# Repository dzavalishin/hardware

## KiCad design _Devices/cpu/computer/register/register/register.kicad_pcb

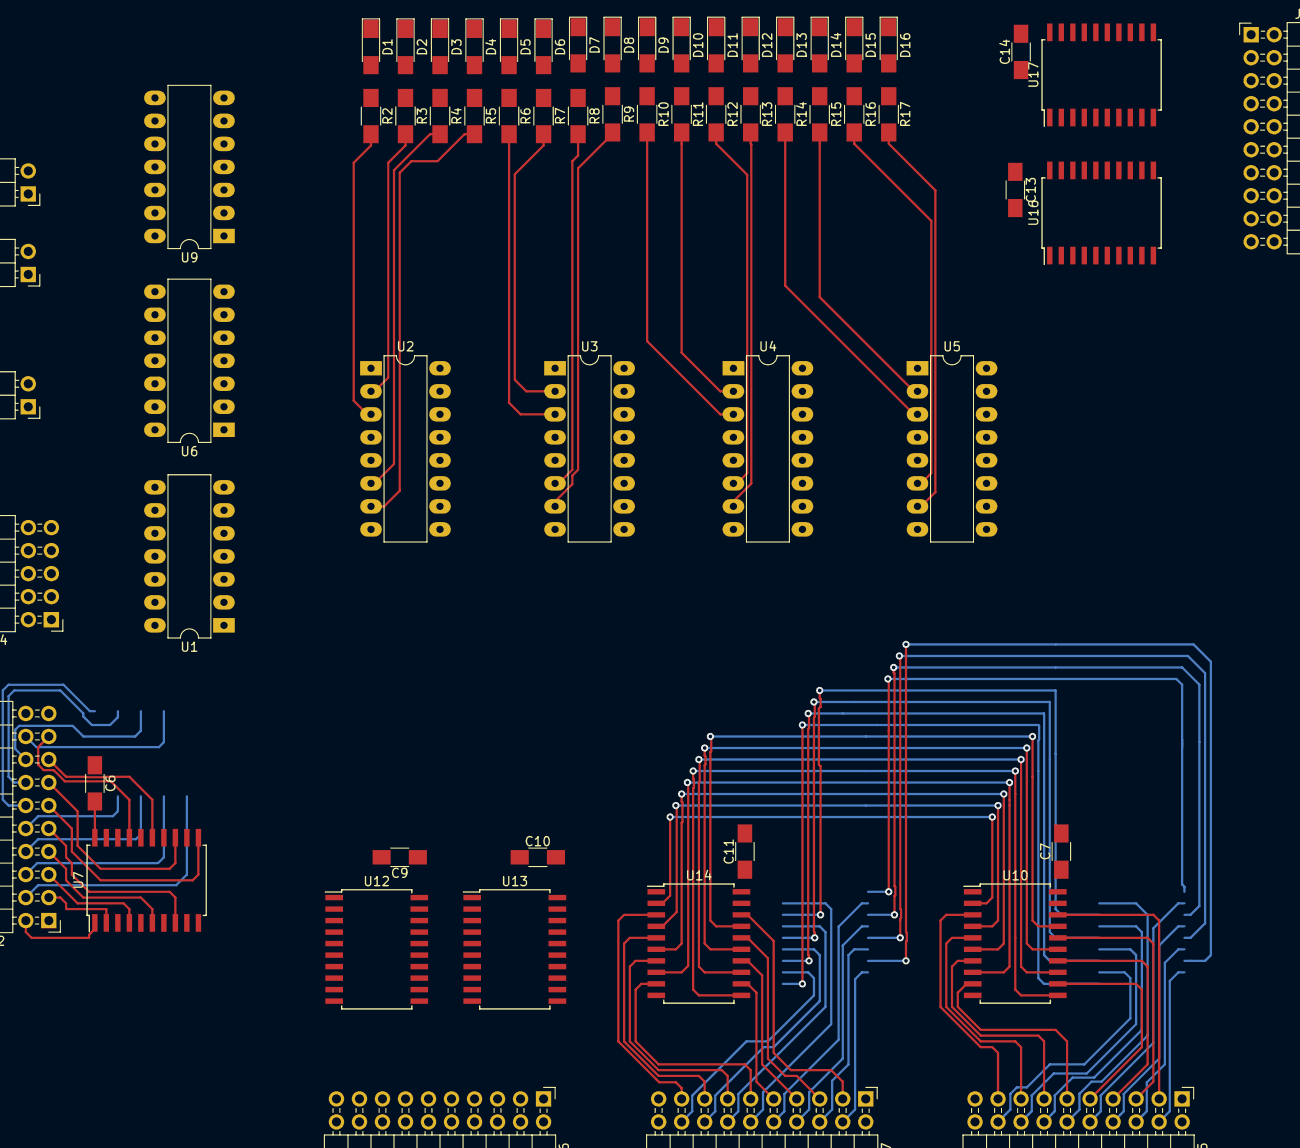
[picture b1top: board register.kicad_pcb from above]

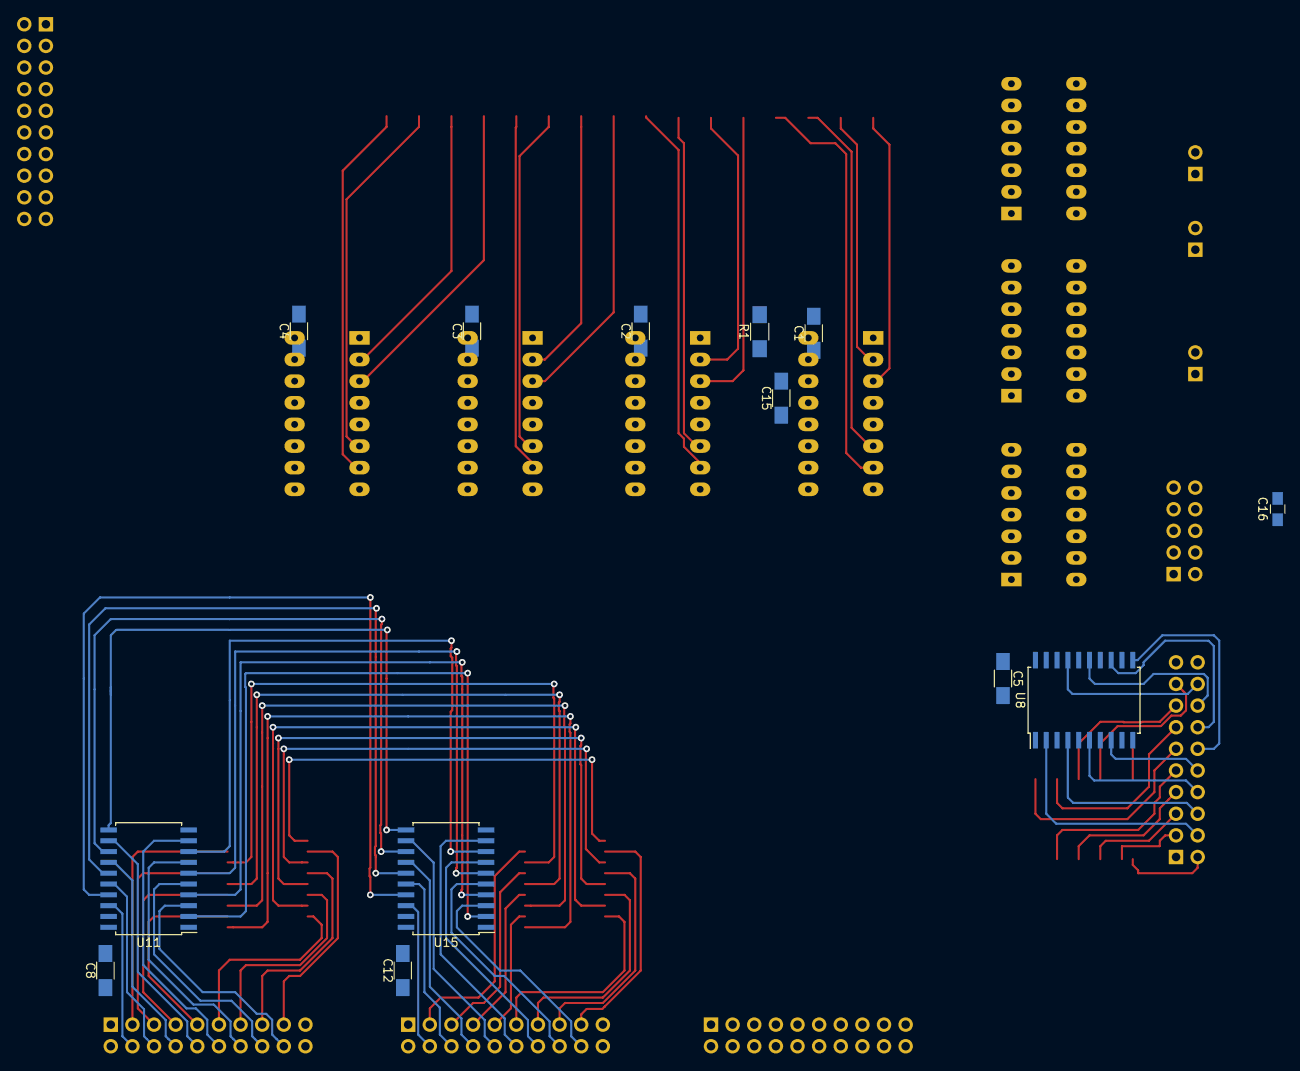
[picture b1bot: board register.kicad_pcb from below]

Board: 2 copper layers, 75 parts (13 on the bottom side), 160 nets.

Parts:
C1, C2, C3, C4, C5, C6, C7, C8, C9, C10, C11, C12, C13, C14, C15: 0,1; C_1206_HandSoldering
C16: 10,0; C_0805_HandSoldering
D1, D2, D3, D4, D5, D6, D7, D8, D9, D10, D11, D12, D13, D14, D15, D16: LED; LED_1206_HandSoldering
J1: ~Select; PinHeader_1x02_P2.54mm_Horizontal
J2: SideIn; PinHeader_2x10_P2.54mm_Horizontal
J3: ~Count; PinHeader_1x02_P2.54mm_Horizontal
J4: Control; PinHeader_2x05_P2.54mm_Horizontal
J5: OutBusB; PinHeader_2x10_P2.54mm_Horizontal
J6: InBus; PinHeader_2x10_P2.54mm_Horizontal
J7: OutBusA; PinHeader_2x10_P2.54mm_Horizontal
J8: OutC; PinHeader_2x10_P2.54mm_Horizontal
J9: ~SideIn; PinHeader_1x02_P2.54mm_Horizontal
R1: 10k; R_1206_HandSoldering
R2, R3, R4, R5, R6, R7, R8, R9, R10, R11, R12, R13, R14, R15, R16, R17: 1k; R_1206_HandSoldering
U1, U6: 74LS00; DIP-14_W7.62mm_LongPads
U2, U3, U4, U5: 74LS193; DIP-16_W7.62mm_LongPads
U7, U8, U10, U11, U12, U13, U14, U15, U16, U17: 74ALS241; SOIC-20W_7.5x12.8mm_Pitch1.27mm
U9: 74LS04; DIP-14_W7.62mm_LongPads

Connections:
+5V: C1.1, C2.1, C3.1, C4.1, C5.1, C6.2, C7.1, C8.2, C9.1, C10.2, C11.1, C12.2, C13.1, C14.2, C15.2, C16.2, J4.9, J4.10, U2.16, U3.16, U4.16, U5.16, U7.20, U8.20, U10.20, U11.20, U12.20, U13.20, U14.20, U15.20, U16.20, U17.20
/Co0: R2.2, U2.3, U10.2, U14.2, U16.2
/Co1: R3.2, U2.2, U10.4, U14.4, U16.4
/Co2: R4.2, U2.6, U10.6, U14.6, U16.6
/Co3: R5.2, U2.7, U10.8, U14.8, U16.8
/Co4: R6.2, U3.3, U10.11, U14.11, U16.11
/Co5: R7.2, U3.2, U10.13, U14.13, U16.13
/Co6: R8.2, U3.6, U10.15, U14.15, U16.15
/Co7: R9.2, U3.7, U10.17, U14.17, U16.17
/Co8: R10.2, U4.3, U11.2, U15.2, U17.2
/Co9: R11.2, U4.2, U11.4, U15.4, U17.4
/Co10: R12.2, U4.6, U11.6, U15.6, U17.6
/Co11: R13.2, U4.7, U11.8, U15.8, U17.8
/Co12: R14.2, U5.3, U11.11, U15.11, U17.11
/Co13: R15.2, U5.2, U11.13, U15.13, U17.13
/Co14: R16.2, U5.6, U11.15, U15.15, U17.15
/Co15: R17.2, U5.7, U11.17, U15.17, U17.17
/Control/Clock: J4.7, U6.12
/Control/CntDnIn: J4.2, U1.9
/Control/CntUpIn: J4.1, U1.1
/Control/Load: J4.8, U6.2
/Control/OutA_Ena: J4.3, U6.10
/Control/OutB_Ena: J4.4, U1.13
/Control/Select: U1.2, U1.10, U1.12, U6.1, U6.9, U9.2
/Di0: U2.15, U7.18, U12.18
/Di1: U2.1, U7.16, U12.16
/Di2: U2.10, U7.14, U12.14
/Di3: U2.9, U7.12, U12.12
/Di4: U3.15, U7.9, U12.9
/Di5: U3.1, U7.7, U12.7
/Di6: U3.10, U7.5, U12.5
/Di7: U3.9, U7.3, U12.3
/Di8: U4.15, U8.18, U13.18
/Di9: U4.1, U8.16, U13.16
/Di10: U4.10, U8.14, U13.14
/Di11: U4.9, U8.12, U13.12
/Di12: U5.15, U8.9, U13.9
/Di13: U5.1, U8.7, U13.7
/Di14: U5.10, U8.5, U13.5
/Di15: U5.9, U8.3, U13.3
/Reset: C15.1, R1.1, U2.14, U3.14, U4.14, U5.14
/~CntDn: U1.8, U2.4
/~CntUp: U2.5, U9.4
/~InBusEna: U6.13, U9.9, U9.10, U12.1, U12.19, U13.1, U13.19
/~Load: U2.11, U3.11, U4.11, U5.11, U9.6
/~OutA_Ena: U6.8, U14.1, U14.19, U15.1, U15.19
/~OutB_Ena: U1.11, U10.1, U10.19, U11.1, U11.19
/~SideInEna: J2.2, J2.19, U7.1, U7.19, U8.1, U8.19, U9.8
GND: C1.2, C2.2, C3.2, C4.2, C5.2, C6.1, C7.2, C8.1, C9.2, C10.1, C11.2, C12.1, C13.2, C14.1, C16.1, D1.1, D2.1, D3.1, D4.1, D5.1, D6.1, D7.1, D8.1, D9.1, D10.1, D11.1, D12.1, D13.1, D14.1, D15.1, D16.1, J1.1, J2.1, J2.20, J3.1, J4.5, J4.6, J5.1, J5.2, J5.19, J5.20, J6.1, J6.2, J6.19, J6.20, J7.1, J7.2, J7.19, J7.20, J8.1, J8.20, J9.1, R1.2, U2.8, U3.8, U4.8, U5.8, U7.10, U8.10, U10.10, U11.10, U12.10, U13.10, U14.10, U15.10, U16.10, U17.10
unnamed: D1.2, R2.1
unnamed: D2.2, R3.1
unnamed: D3.2, R4.1
unnamed: D4.2, R5.1
unnamed: D5.2, R6.1
unnamed: D6.2, R7.1
unnamed: D7.2, R8.1
unnamed: D8.2, R9.1
unnamed: D9.2, R10.1
unnamed: D10.2, R11.1
unnamed: D11.2, R12.1
unnamed: D12.2, R13.1
unnamed: D13.2, R14.1
unnamed: D14.2, R15.1
unnamed: D15.2, R16.1
unnamed: D16.2, R17.1
unnamed: J1.2, U9.1
unnamed: J2.3, U7.2
unnamed: J2.4, U8.2
unnamed: J2.5, U7.4
unnamed: J2.6, U8.4
unnamed: J2.7, U7.6
unnamed: J2.8, U8.6
unnamed: J2.9, U7.8
unnamed: J2.10, U8.8
unnamed: J2.11, U7.11
unnamed: J2.12, U8.11
unnamed: J2.13, U7.13
unnamed: J2.14, U8.13
unnamed: J2.15, U7.15
unnamed: J2.16, U8.15
unnamed: J2.17, U7.17
unnamed: J2.18, U8.17
unnamed: J3.2, U1.5
unnamed: J5.3, U10.18
unnamed: J5.4, U11.18
unnamed: J5.5, U10.16
unnamed: J5.6, U11.16
unnamed: J5.7, U10.14
unnamed: J5.8, U11.14
unnamed: J5.9, U10.12
unnamed: J5.10, U11.12
unnamed: J5.11, U10.9
unnamed: J5.12, U11.9
unnamed: J5.13, U10.7
unnamed: J5.14, U11.7
unnamed: J5.15, U10.5
unnamed: J5.16, U11.5
unnamed: J5.17, U10.3
unnamed: J5.18, U11.3
unnamed: J6.3, U12.2
unnamed: J6.4, U13.2
unnamed: J6.5, U12.4
unnamed: J6.6, U13.4
unnamed: J6.7, U12.6
unnamed: J6.8, U13.6
unnamed: J6.9, U12.8
unnamed: J6.10, U13.8
unnamed: J6.11, U12.11
unnamed: J6.12, U13.11
unnamed: J6.13, U12.13
unnamed: J6.14, U13.13
unnamed: J6.15, U12.15
unnamed: J6.16, U13.15
unnamed: J6.17, U12.17
unnamed: J6.18, U13.17
unnamed: J7.3, U14.18
unnamed: J7.4, U15.18
unnamed: J7.5, U14.16
unnamed: J7.6, U15.16
unnamed: J7.7, U14.14
unnamed: J7.8, U15.14
unnamed: J7.9, U14.12
unnamed: J7.10, U15.12
unnamed: J7.11, U14.9
unnamed: J7.12, U15.9
unnamed: J7.13, U14.7
unnamed: J7.14, U15.7
unnamed: J7.15, U14.5
unnamed: J7.16, U15.5
unnamed: J7.17, U14.3
unnamed: J7.18, U15.3
unnamed: J8.3, U16.18
unnamed: J8.4, U17.18
unnamed: J8.5, U16.16
unnamed: J8.6, U17.16
unnamed: J8.7, U16.14
unnamed: J8.8, U17.14
unnamed: J8.9, U16.12
unnamed: J8.10, U17.12
unnamed: J8.11, U16.9
unnamed: J8.12, U17.9
unnamed: J8.13, U16.7
unnamed: J8.14, U17.7
unnamed: J8.15, U16.5
unnamed: J8.16, U17.5
unnamed: J8.17, U16.3
unnamed: J8.18, U17.3
unnamed: J8.2, J8.19, U16.1, U16.19, U17.1, U17.19
unnamed: J9.2, U9.11
unnamed: U1.3, U1.4
unnamed: U1.6, U9.3
unnamed: U2.12, U3.5
unnamed: U2.13, U3.4
unnamed: U3.12, U4.5
unnamed: U3.13, U4.4
unnamed: U4.12, U5.5
unnamed: U4.13, U5.4
unnamed: U6.3, U6.4
unnamed: U6.6, U9.5
unnamed: U6.5, U6.11

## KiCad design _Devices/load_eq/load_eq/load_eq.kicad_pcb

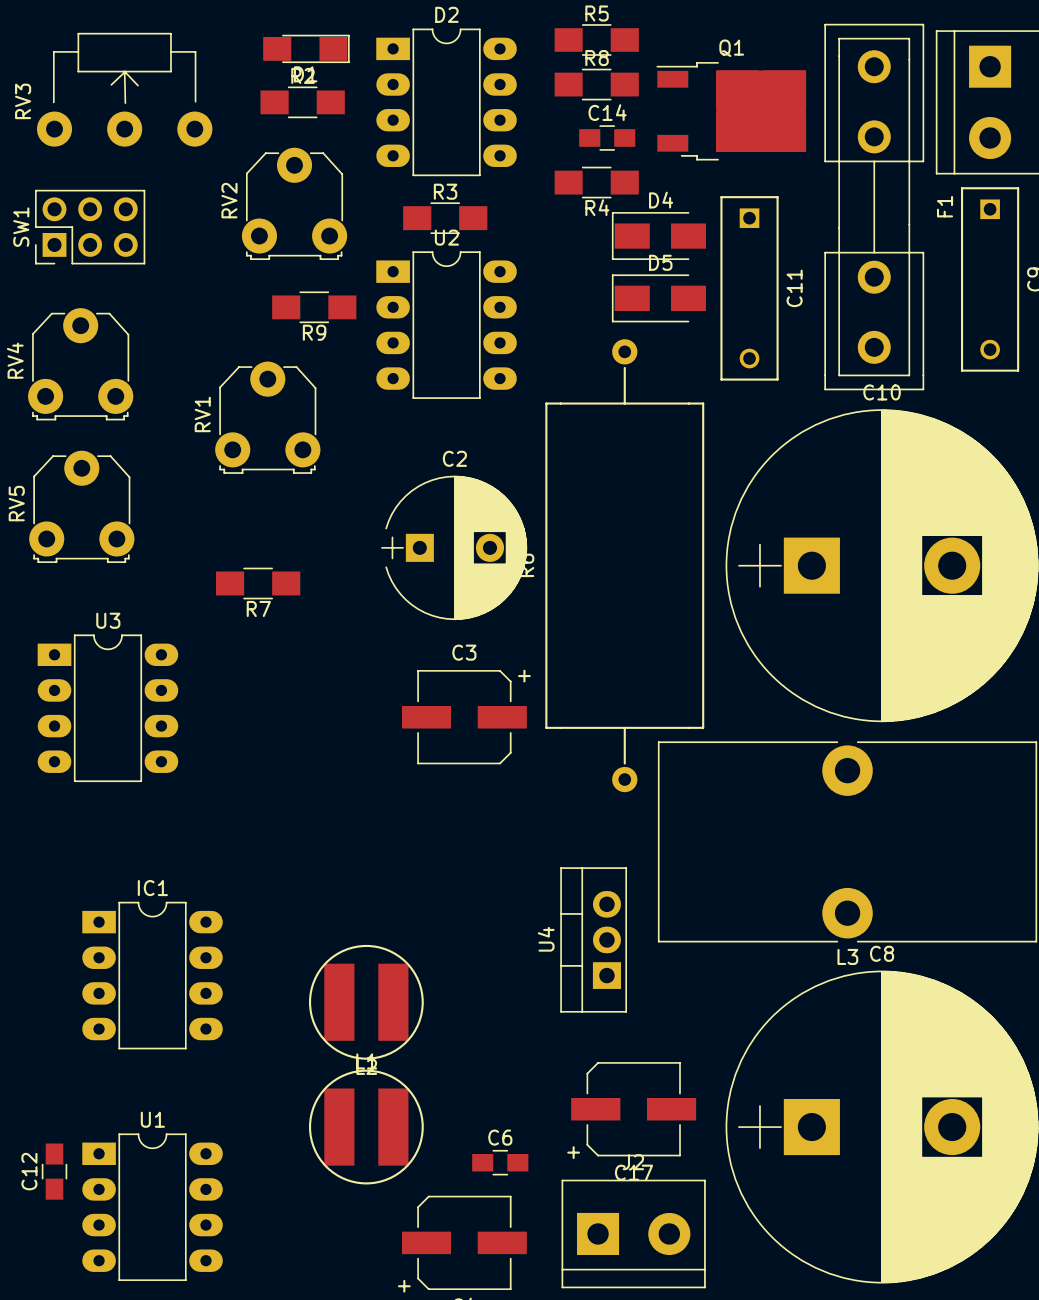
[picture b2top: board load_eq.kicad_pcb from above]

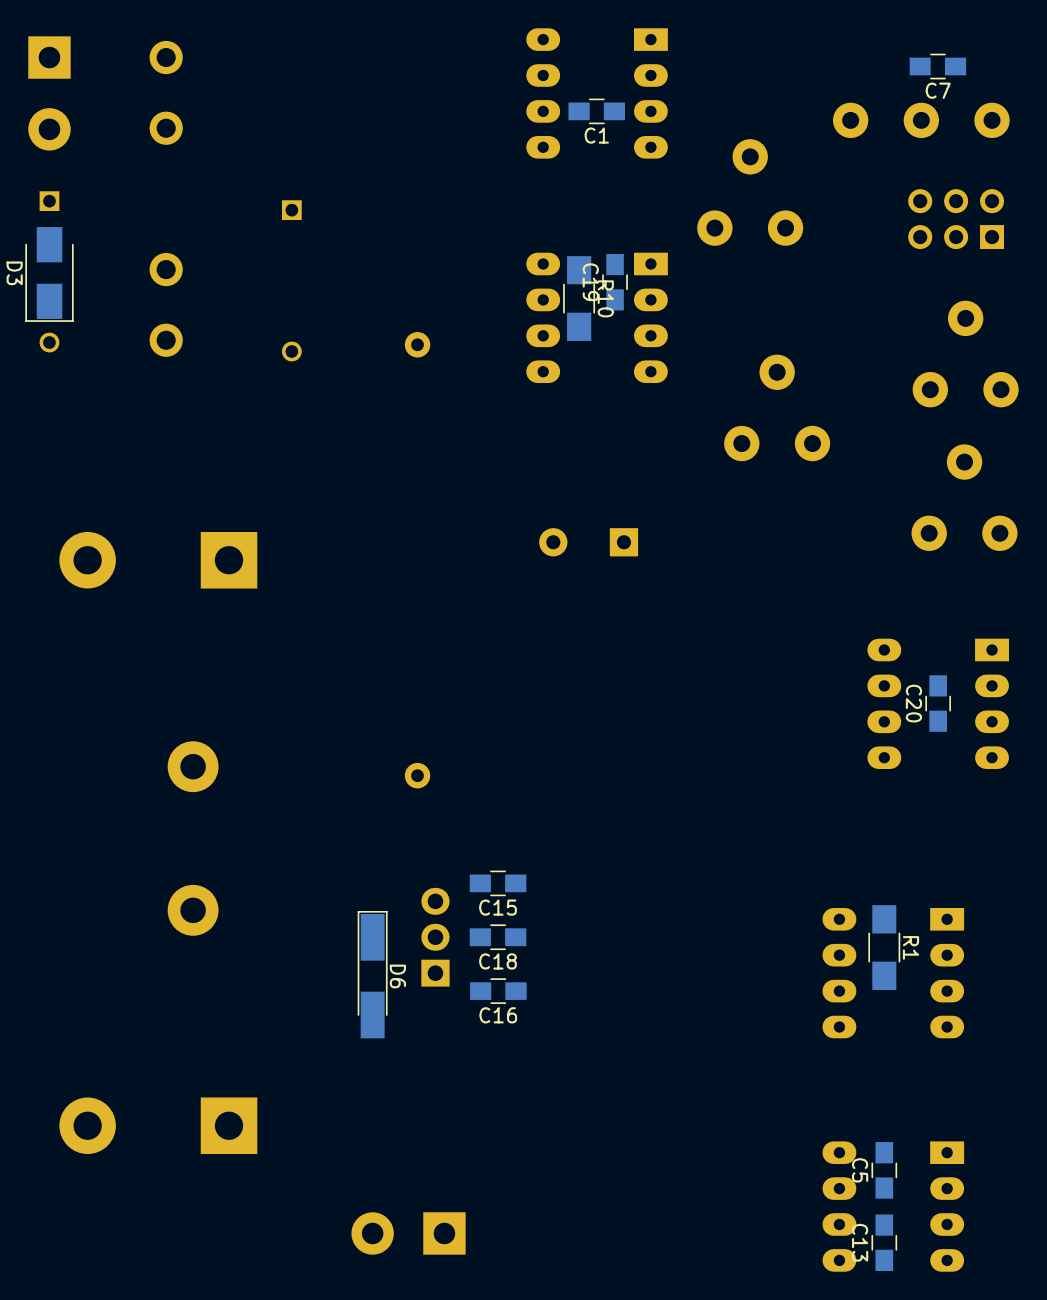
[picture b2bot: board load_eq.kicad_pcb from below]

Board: 2 copper layers, 54 parts (13 on the bottom side), 31 nets, no tracks yet.

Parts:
C1, C5, C6, C7, C13, C19, C20: 0,1; C_0805_HandSoldering
C2: 220,0; CP_Radial_D10.0mm_P5.00mm
C3, C4, C17: 100,0; CP_Elec_6.3x5.3
C8, C10: 4700,0 40v; CP_Radial_D22.0mm_P10.00mm_SnapIn
C9: 1uF; C_Rect_L13_W4_P10
C11: 1uF 250v; C_Rect_L13_W4_P10
C12: 0,01; C_0805_HandSoldering
C14: 10uF NP; C_0805_HandSoldering
C15, C16, C18: 0,33; C_0805_HandSoldering
D1: LED; LED_1206_HandSoldering
D2: 170АП3; DIP-8_W7.62mm_LongPads
D3, D4, D5: D; D_SMA
D6: 4v7; D_MiniMELF_Handsoldering
F1: Fuse; Fuseholder5x20_horiz_open_inline_Type-I
IC1: KP504HT4; DIP-8_W7.62mm_LongPads
J1: Load; TerminalBlock_bornier-2_P5.08mm
J2: +12; TerminalBlock_bornier-2_P5.08mm
L1, L2: 100uH; cd54
L3: 100uH; L_Toroid_Vertical_L26.7mm_W14.0mm_P10.16mm_Pulse_D
Q1: IRFR024N; TO-252-2
R1, R3, R4, R7, R9: 1k; R_1206_HandSoldering
R2: 2,2k; R_1206_HandSoldering
R5, R8: 18; R_1206_HandSoldering
R6: R_US; Resistor_Ceramic_Horizontal_L23mm-W9mm-H9mm-p30mm
R10: 100k; R_1206_HandSoldering
RV1: 10k; Potentiometer_Triwood_RM-065
RV2, RV4, RV5: 500; Potentiometer_Triwood_RM-065
RV3: 1k; Potentiometer_WirePads_largePads
SW1: X1-X0,1; PinHeader_2x03_P2.54mm_Vertical
U1: ICM7555; DIP-8_W7.62mm_LongPads
U2: LM2903; DIP-8_W7.62mm_LongPads
U3: MCP602; DIP-8_W7.62mm_LongPads
U4: L7805; TO-220-3_Vertical

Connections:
+10V: C4.1, C5.2, C6.1, C19.2, C20.2, IC1.8, L2.2, R1.1, R2.2, R3.2, R4.2, R10.1, RV1.1, RV1.2, SW1.5, U1.4, U1.8, U2.8, U3.8
/+10REG: C3.1, C15.2, L1.2, L2.1, U4.3
GND: C1.1, C2.2, C3.2, C4.2, C5.1, C6.2, C7.1, C12.2, C13.2, C14.1, C15.1, C16.1, C17.2, C18.1, C19.1, C20.1, D2.3, D5.1, D6.2, IC1.3, J2.2, RV4.2, RV4.3, RV5.1, RV5.2, U1.1, U2.4, U2.5, U3.4, U3.5
unnamed: C1.2, C2.1, D2.6, L1.1
unnamed: C7.2, R9.2, RV3.2
unnamed: C8.1, L3.1, R6.1
unnamed: C9.2, C10.1, D3.1, F1.2, L3.2
unnamed: C8.2, C9.1, C10.2, C11.1, C14.2, D3.2, D4.2, J1.2, Q1.3, R4.1
unnamed: C11.2, Q1.2, R6.2
unnamed: C12.1, IC1.2, U1.2, U1.6, U1.7, U3.3
unnamed: C13.1, U1.5
unnamed: C16.2, C17.1, J2.1, U4.1
unnamed: C18.2, D6.1, U4.2
unnamed: D1.1, D2.2, D2.4, R3.1, U2.1
unnamed: D1.2, R2.1
unnamed: D2.5, R8.1
unnamed: D2.7, R5.1
unnamed: D4.1, D5.2
unnamed: F1.1, J1.1
unnamed: IC1.1, R1.2
unnamed: Q1.1, R5.2, R8.2
unnamed: R7.1, U2.3
unnamed: R7.2, U3.1, U3.2
unnamed: R9.1, U2.2
unnamed: R10.2, U2.6
unnamed: RV1.3, RV2.1, RV2.2, SW1.4
unnamed: RV2.3, RV3.3
unnamed: RV3.1, SW1.2
unnamed: RV4.1, SW1.1
unnamed: RV5.3, SW1.3
unnamed: U3.6, U3.7

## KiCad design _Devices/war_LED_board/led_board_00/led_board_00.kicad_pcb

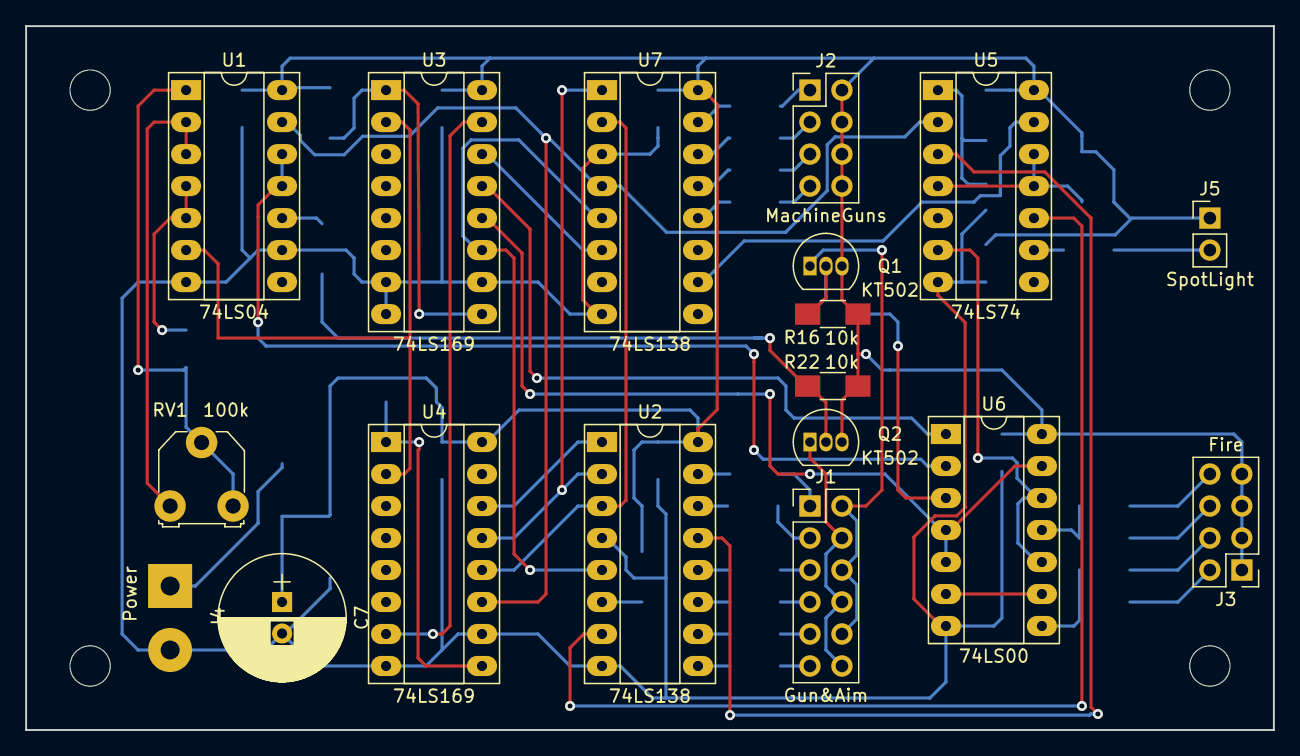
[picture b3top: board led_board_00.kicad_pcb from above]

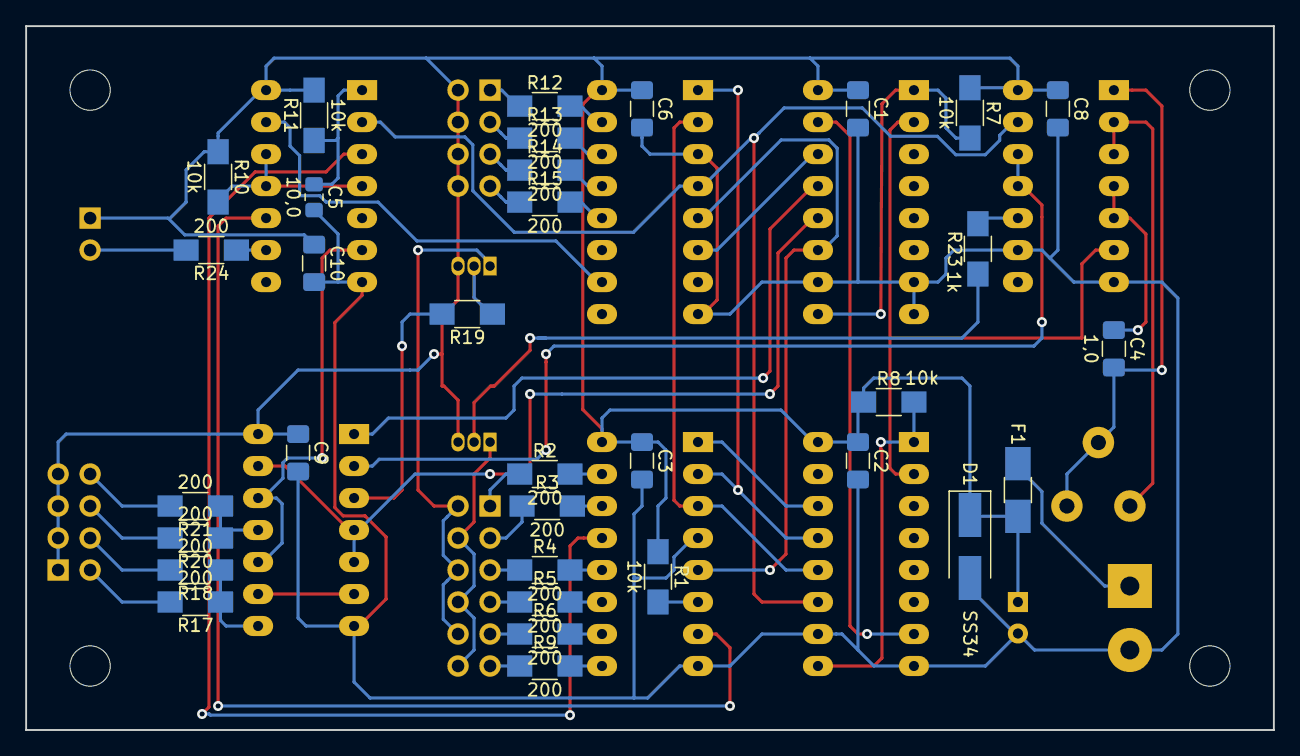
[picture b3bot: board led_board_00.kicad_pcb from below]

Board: 2 copper layers, 99.1 x 55.9 mm, 55 parts (33 on the bottom side), 61 nets.

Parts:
C1, C2, C3, C6, C8, C9, C10: 0,1; C_1206_3216Metric_Pad1.42x1.75mm_HandSolder
C4: 1,0; C_1206_3216Metric_Pad1.42x1.75mm_HandSolder
C5: 10,0; C_0805_2012Metric_Pad1.15x1.40mm_HandSolder
C7: 100,0; CP_Radial_D10.0mm_P2.50mm
D1: SS34; D_SMA_Handsoldering
F1: Polyfuse; Fuse_SMD1206_HandSoldering
J1: Gun&Aim; PinHeader_2x06_P2.54mm_Vertical
J2: MachineGuns; PinHeader_2x04_P2.54mm_Vertical
J3: Fire; PinHeader_2x04_P2.54mm_Vertical
J4: Power; SolderWirePad_1x02_P5.08mm_Drill1.5mm
J5: SpotLight; PinHeader_1x02_P2.54mm_Vertical
MH1, MH2, MH3, MH4: -; MountingHole_3.2mm_M3
Q1, Q2: KT502; TO-92_Inline
R1, R7, R8, R10, R11, R16, R22: 10k; R_1206_HandSoldering
R2, R3, R4, R5, R6, R9, R12, R13, R14, R15, R17, R18, R20, R21, R24: 200; R_1206_HandSoldering
R19, R23: 1k; R_1206_HandSoldering
RV1: 100k; Potentiometer_Triwood_RM-065
U1: 74LS04; DIP-14_W7.62mm_Socket_LongPads
U2, U7: 74LS138; DIP-16_W7.62mm_Socket_LongPads
U3, U4: 74LS169; DIP-16_W7.62mm_Socket_LongPads
U5: 74LS74; DIP-14_W7.62mm_Socket_LongPads
U6: 74LS00; DIP-14_W7.62mm_Socket_LongPads

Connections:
+5V: C1.1, C2.1, C3.1, C6.1, C7.1, C8.1, C9.1, C10.1, D1.1, F1.1, J2.2, J2.4, J2.6, J2.8, J3.1, J3.3, J3.5, J3.7, J5.1, Q1.3, Q2.3, R1.1, R7.1, R8.1, R10.1, R11.2, R16.1, R22.1, U1.14, U2.16, U3.16, U4.16, U5.14, U6.14, U7.16
/ClkA: U3.14, U7.6
/ClkB: U3.13, U6.1
/ClkC: U3.12, U6.4, U6.5, U6.13
/ClkD: U2.5, U3.11, U7.5
/Up1: J1.2, J1.6, J1.10, Q1.1
/Up2: J1.4, J1.8, J1.12, Q2.1
GND: C1.2, C2.2, C3.2, C5.2, C6.2, C7.2, C8.2, C9.2, C10.2, D1.2, J4.2, U1.7, U1.9, U2.4, U2.8, U3.7, U3.8, U3.10, U4.8, U4.10, U5.7, U6.7, U7.3, U7.8
unnamed: C4.1, U1.4, U1.5
unnamed: C4.2, RV1.2, RV1.3, U1.1
unnamed: C5.1, R11.1, U5.1
unnamed: F1.2, J4.1
unnamed: J1.1, R2.1
unnamed: J1.3, R3.1
unnamed: J1.5, R4.1
unnamed: J1.7, R5.1
unnamed: J1.9, R6.1
unnamed: J1.11, R9.1
unnamed: J2.1, R12.1
unnamed: J2.3, R13.1
unnamed: J2.5, R14.1
unnamed: J2.7, R15.1
unnamed: J3.2, R17.2
unnamed: J3.4, R18.2
unnamed: J3.6, R20.2
unnamed: J3.8, R21.2
unnamed: J5.2, R24.2
unnamed: Q1.2, R16.2, R19.1
unnamed: Q2.2, R22.2, R23.1
unnamed: R1.2, U2.6
unnamed: R2.2, U2.15
unnamed: R3.2, U2.14
unnamed: R4.2, U2.12
unnamed: R5.2, U2.11
unnamed: R6.2, U2.10
unnamed: R7.2, U3.1, U3.9
unnamed: R8.2, U4.1, U4.9
unnamed: R9.2, U2.9
unnamed: R10.2, U5.4, U5.11, U5.12
unnamed: R12.2, U7.15
unnamed: R13.2, U7.14
unnamed: R14.2, U7.13
unnamed: R15.2, U7.12
unnamed: R17.1, R18.1, U6.8
unnamed: R19.2, U6.3
unnamed: R20.1, R21.1, U6.11
unnamed: R23.2, U1.10
unnamed: R24.1, U5.9
unnamed: RV1.1, U1.2, U1.3
unnamed: U1.6, U3.2, U4.2
unnamed: U1.11, U1.12, U6.2
unnamed: U1.13, U4.11, U5.2, U7.4
unnamed: U2.1, U4.14
unnamed: U2.2, U4.13, U7.1
unnamed: U2.3, U4.12, U7.2
unnamed: U2.7, U5.10
unnamed: U2.13, U5.3
unnamed: U3.15, U4.7
unnamed: U5.6, U6.10, U6.12
unnamed: U5.13, U7.10
unnamed: U6.6, U6.9

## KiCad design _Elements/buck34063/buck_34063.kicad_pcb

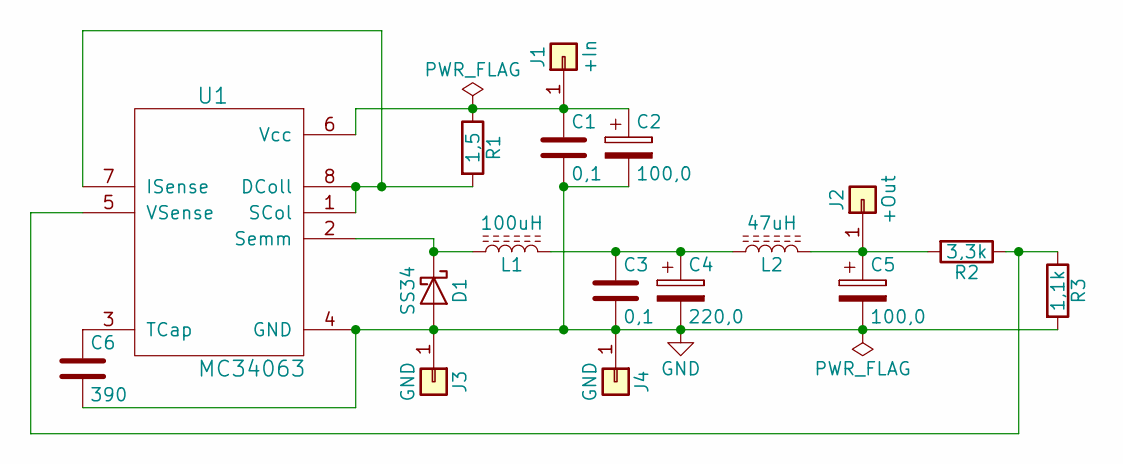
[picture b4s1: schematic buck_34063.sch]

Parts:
C1, C3: 0,1; C_1206_HandSoldering
C2, C5: 100,0; CP_Elec_6.3x5.7
C4: 220,0; CP_Elec_6.3x5.7
C6: 390; C_1206_HandSoldering
D1: SS34; D_SMB-SMC_Universal_Handsoldering
J1: +In; Pin_Header_Straight_1x01_Pitch2.54mm
J2: +Out; Pin_Header_Straight_1x01_Pitch2.54mm
J3, J4: GND; Pin_Header_Straight_1x01_Pitch2.54mm
L1: 100uH; Choke_SMD_6.3x6.3_H3
L2: 47uH; Choke_SMD_1206_Handsoldering
R1: 1,5; R_2512_HandSoldering
R2: 3,3k; R_1206_HandSoldering
R3: 1,1k; R_1206_HandSoldering
U1: MC34063; SO-8_5.3x6.2mm_Pitch1.27mm

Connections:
GND: C1.2, C2.2, C3.2, C4.2, C5.2, C6.2, D1.2 (A), J3.1, J4.1, R3.2, U1.4 (GND)
unnamed: C1.1, C2.1, J1.1, R1.1, U1.6 (Vcc)
unnamed: C3.1, C4.1, L1.2, L2.1
unnamed: C5.1, J2.1, L2.2, R2.2
unnamed: C6.1, U1.3 (TCap)
unnamed: D1.1 (K), L1.1, U1.2 (Semm)
unnamed: R1.2, U1.1 (SCol), U1.7 (ISense), U1.8 (DColl)
unnamed: R2.1, R3.1, U1.5 (VSense)

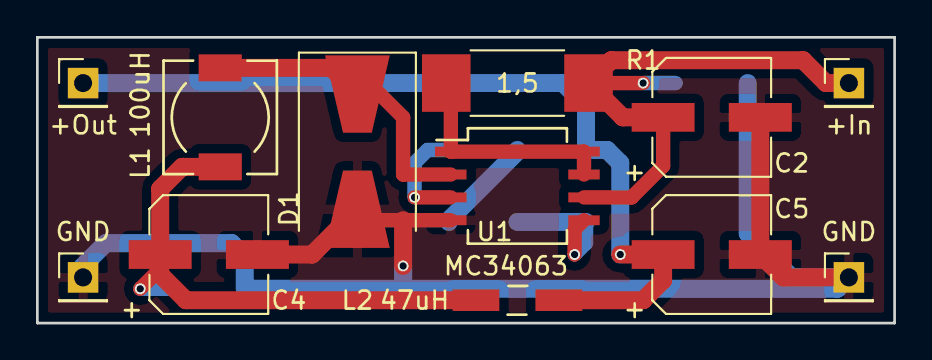
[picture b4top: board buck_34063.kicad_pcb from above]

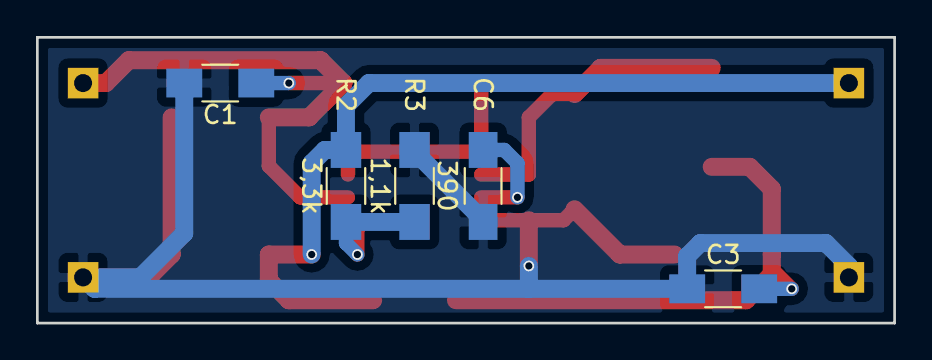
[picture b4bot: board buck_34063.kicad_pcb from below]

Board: 2 copper layers, 47.6 x 15.9 mm, 17 parts (5 on the bottom side), 8 nets.

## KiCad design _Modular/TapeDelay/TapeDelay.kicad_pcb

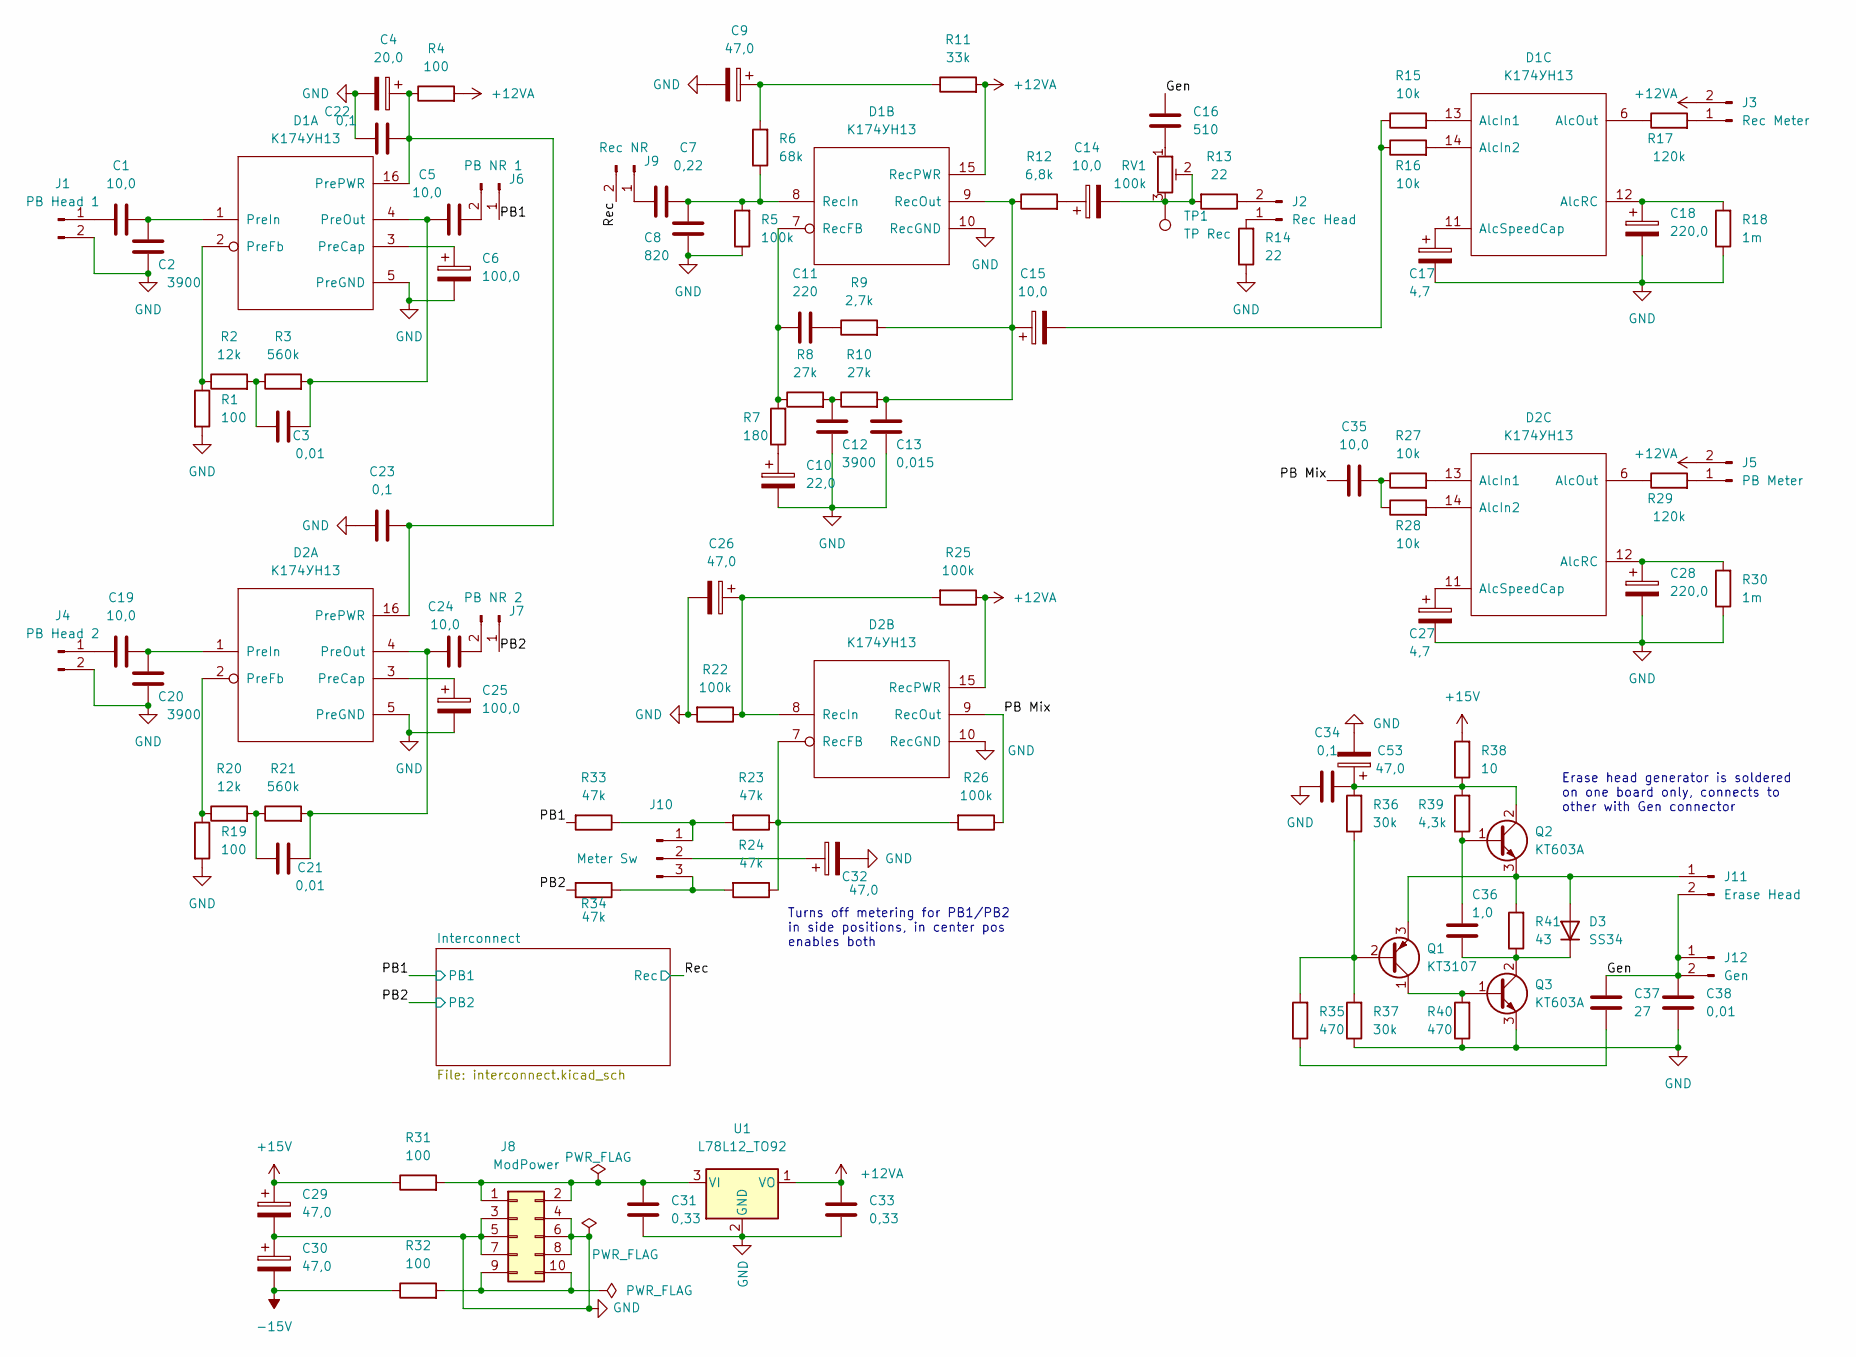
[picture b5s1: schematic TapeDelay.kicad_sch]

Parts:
C1, C5, C15, C19, C24, C35: 10,0; C_0805_2012Metric_Pad1.18x1.45mm_HandSolder
C2, C12, C20: 3900; C_0805_2012Metric_Pad1.18x1.45mm_HandSolder
C3, C21: 0,01; C_0805_2012Metric_Pad1.18x1.45mm_HandSolder
C4: 20,0; CP_Radial_D5.0mm_P2.50mm
C6, C25: 100,0; CP_Radial_D7.5mm_P2.50mm
C7: 0,22; C_0805_2012Metric_Pad1.18x1.45mm_HandSolder
C8: 820; C_0805_2012Metric_Pad1.18x1.45mm_HandSolder
C9, C26, C29, C30, C32, C53: 47,0; CP_Radial_D6.3mm_P2.50mm
C10: 22,0; C_0805_2012Metric_Pad1.18x1.45mm_HandSolder
C11: 220; C_0805_2012Metric_Pad1.18x1.45mm_HandSolder
C13: 0,015; C_0805_2012Metric_Pad1.18x1.45mm_HandSolder
C14: 10,0; CP_Radial_D5.0mm_P2.50mm
C16: 510; C_0805_2012Metric_Pad1.18x1.45mm_HandSolder
C17, C27: 4,7; C_0805_2012Metric_Pad1.18x1.45mm_HandSolder
C18, C28: 220,0; CP_Radial_D7.5mm_P2.50mm
C22, C23: 0,1; C_1206_3216Metric_Pad1.33x1.80mm_HandSolder
C31, C33: 0,33; C_0805_2012Metric_Pad1.18x1.45mm_HandSolder
C34: 0,1; C_0805_2012Metric_Pad1.18x1.45mm_HandSolder
C36: 1,0; C_0805_2012Metric_Pad1.18x1.45mm_HandSolder
C37: 27; C_Disc_D5.0mm_W2.5mm_P2.50mm
C38: 0,01; C_Disc_D5.0mm_W2.5mm_P2.50mm
D1, D2: К174УН13; DIP-16_W7.62mm_LongPads
D3: SS34; D_SMA-SMB_Universal_Handsoldering
J1: PB Head 1; PinHeader_1x02_P2.54mm_Vertical
J2: Rec Head; PinHeader_1x02_P2.54mm_Vertical
J3: Rec Meter; PinHeader_1x02_P2.54mm_Vertical
J4: PB Head 2; PinHeader_1x02_P2.54mm_Vertical
J5: PB Meter; PinHeader_1x02_P2.54mm_Vertical
J6: PB NR 1; PinHeader_1x02_P2.54mm_Vertical
J7: PB NR 2; PinHeader_1x02_P2.54mm_Vertical
J8: ModPower; PinHeader_2x05_P2.54mm_Vertical
J9: Rec NR; PinHeader_1x02_P2.54mm_Vertical
J10: Meter Sw; PinHeader_1x03_P2.54mm_Vertical
J11: Erase Head; PinHeader_1x02_P2.54mm_Vertical
J12: Gen; PinHeader_1x02_P2.54mm_Vertical
Q1: KT3107; TO-92
Q2, Q3: KT603A; TO-92_Wide
R1, R4, R19, R31, R32: 100; R_1206_3216Metric_Pad1.30x1.75mm_HandSolder
R2, R20: 12k; R_1206_3216Metric_Pad1.30x1.75mm_HandSolder
R3, R21: 560k; R_1206_3216Metric_Pad1.30x1.75mm_HandSolder
R5, R22, R25, R26: 100k; R_1206_3216Metric_Pad1.30x1.75mm_HandSolder
R6: 68k; R_1206_3216Metric_Pad1.30x1.75mm_HandSolder
R7: 180; R_1206_3216Metric_Pad1.30x1.75mm_HandSolder
R8, R10: 27k; R_1206_3216Metric_Pad1.30x1.75mm_HandSolder
R9: 2,7k; R_1206_3216Metric_Pad1.30x1.75mm_HandSolder
R11: 33k; R_1206_3216Metric_Pad1.30x1.75mm_HandSolder
R12: 6,8k; R_1206_3216Metric_Pad1.30x1.75mm_HandSolder
R13, R14: 22; R_Axial_DIN0309_L9.0mm_D3.2mm_P2.54mm_Vertical
R15, R16, R27, R28: 10k; R_1206_3216Metric_Pad1.30x1.75mm_HandSolder
R17, R29: 120k; R_1206_3216Metric_Pad1.30x1.75mm_HandSolder
R18, R30: 1m; R_1206_3216Metric_Pad1.30x1.75mm_HandSolder
R23, R24, R33, R34: 47k; R_1206_3216Metric_Pad1.30x1.75mm_HandSolder
R35, R40: 470; R_1206_3216Metric_Pad1.30x1.75mm_HandSolder
R36, R37: 30k; R_1206_3216Metric_Pad1.30x1.75mm_HandSolder
R38: 10; R_Axial_DIN0309_L9.0mm_D3.2mm_P2.54mm_Vertical
R39: 4,3k; R_1206_3216Metric_Pad1.30x1.75mm_HandSolder
R41: 43; R_Axial_DIN0309_L9.0mm_D3.2mm_P2.54mm_Vertical
RV1: 100k; Potentiometer_Runtron_RM-065_Vertical
TP1: TP Rec; PinHeader_1x01_P2.54mm_Vertical
U1: L78L12_TO92; TO-92_Inline

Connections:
+12VA: C33.2, D1.15 (RecPWR), D2.15 (RecPWR), J3.2, J5.2, R4.2, R11.2, R25.1, U1.1 (VO)
+15V: C29.1, R31.1, R38.2; also elsewhere on the board
-15V: C30.2, R32.1; also elsewhere on the board
/Gen: C16.2, C37.2, C38.2, J11.2, J12.1, J12.2
/PB1: J6.1, R33.2; also elsewhere on the board
/PB2: J7.1, R34.2; also elsewhere on the board
/PB Mix: C35.1, D2.9 (RecOut), R26.1
/Rec: J9.2; also elsewhere on the board
GND: C2.2, C4.2, C6.2, C8.2, C9.2, C10.2, C12.2, C13.2, C17.2, C18.2, C20.2, C22.1, C23.1, C25.2, C26.2, C27.2, C28.2, C29.2, C30.1, C31.1, C32.2, C33.1, C34.2, C38.1, C53.2, D1.5 (PreGND), D1.10 (RecGND), D2.5 (PreGND), D2.10 (RecGND), J1.2, J4.2, J8.3, J8.4, J8.5, J8.6, J8.7, J8.8, Q3.3 (E), R1.2, R5.1, R14.1, R18.1, R19.2, R22.2, R30.1, R37.1, R40.1, U1.2 (GND); also elsewhere on the board
unnamed: C1.1, J1.1
unnamed: C1.2, C2.1, D1.1 (PreIn)
unnamed: C3.1, R2.2, R3.1
unnamed: C3.2, C5.1, D1.4 (PreOut), R3.2
unnamed: C5.2, J6.2
unnamed: C6.1, D1.3 (PreCap)
unnamed: C7.1, J9.1
unnamed: C7.2, C8.1, D1.8 (RecIn), R5.2, R6.1
unnamed: C9.1, R6.2, R11.1
unnamed: C10.1, R7.1
unnamed: C11.1, D1.7 (RecFB), R7.2, R8.1
unnamed: C11.2, R9.1
unnamed: C12.1, R8.2, R10.1
unnamed: C13.1, C15.1, D1.9 (RecOut), R9.2, R10.2, R12.1
unnamed: C14.1, R12.2
unnamed: C15.2, R15.1, R16.1
unnamed: C16.1, RV1.1
unnamed: C17.1, D1.11 (AlcSpeedCap)
unnamed: C18.1, D1.12 (AlcRC), R18.2
unnamed: C19.1, J4.1
unnamed: C19.2, C20.1, D2.1 (PreIn)
unnamed: C21.1, R20.2, R21.1
unnamed: C21.2, C24.1, D2.4 (PreOut), R21.2
unnamed: C4.1, C22.2, C23.2, D1.16 (PrePWR), D2.16 (PrePWR), R4.1
unnamed: C24.2, J7.2
unnamed: C25.1, D2.3 (PreCap)
unnamed: C26.1, D2.8 (RecIn), R22.1, R25.2
unnamed: C27.1, D2.11 (AlcSpeedCap)
unnamed: C28.1, D2.12 (AlcRC), R30.2
unnamed: C31.2, J8.1, J8.2, R31.2, U1.3 (VI)
unnamed: C32.1, J10.2
unnamed: C34.1, C53.1, Q2.2 (C), R36.2, R38.1, R39.2
unnamed: C35.2, R27.1, R28.1
unnamed: C36.1, D3.1 (K), Q3.2 (C), R41.1
unnamed: C36.2, Q2.1 (B), R39.1
unnamed: C37.1, R35.1
unnamed: D1.2 (PreFb), R1.1, R2.1
unnamed: D1.6 (AlcOut), R17.1
unnamed: D1.13 (AlcIn1), R15.2
unnamed: D1.14 (AlcIn2), R16.2
unnamed: D2.2 (PreFb), R19.1, R20.1
unnamed: D2.6 (AlcOut), R29.1
unnamed: D2.7 (RecFB), R23.1, R24.1, R26.2
unnamed: D2.13 (AlcIn1), R27.2
unnamed: D2.14 (AlcIn2), R28.2
unnamed: D3.2 (A), J11.1, Q1.3 (E), Q2.3 (E), R41.2
unnamed: J2.1, R14.2
unnamed: J2.2, R13.1
unnamed: J3.1, R17.2
unnamed: J5.1, R29.2
unnamed: J8.9, J8.10, R32.2
unnamed: J10.1, R23.2, R33.1
unnamed: J10.3, R24.2, R34.1
unnamed: Q1.1 (C), Q3.1 (B), R40.2
unnamed: Q1.2 (B), R35.2, R36.1, R37.2
unnamed: C14.2, R13.2, RV1.2, RV1.3, TP1.1

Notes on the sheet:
Erase head generator is soldered on one board only, connects to other with Gen connector
Turns off metering for PB1/PB2 in side positions, in center pos enables both
